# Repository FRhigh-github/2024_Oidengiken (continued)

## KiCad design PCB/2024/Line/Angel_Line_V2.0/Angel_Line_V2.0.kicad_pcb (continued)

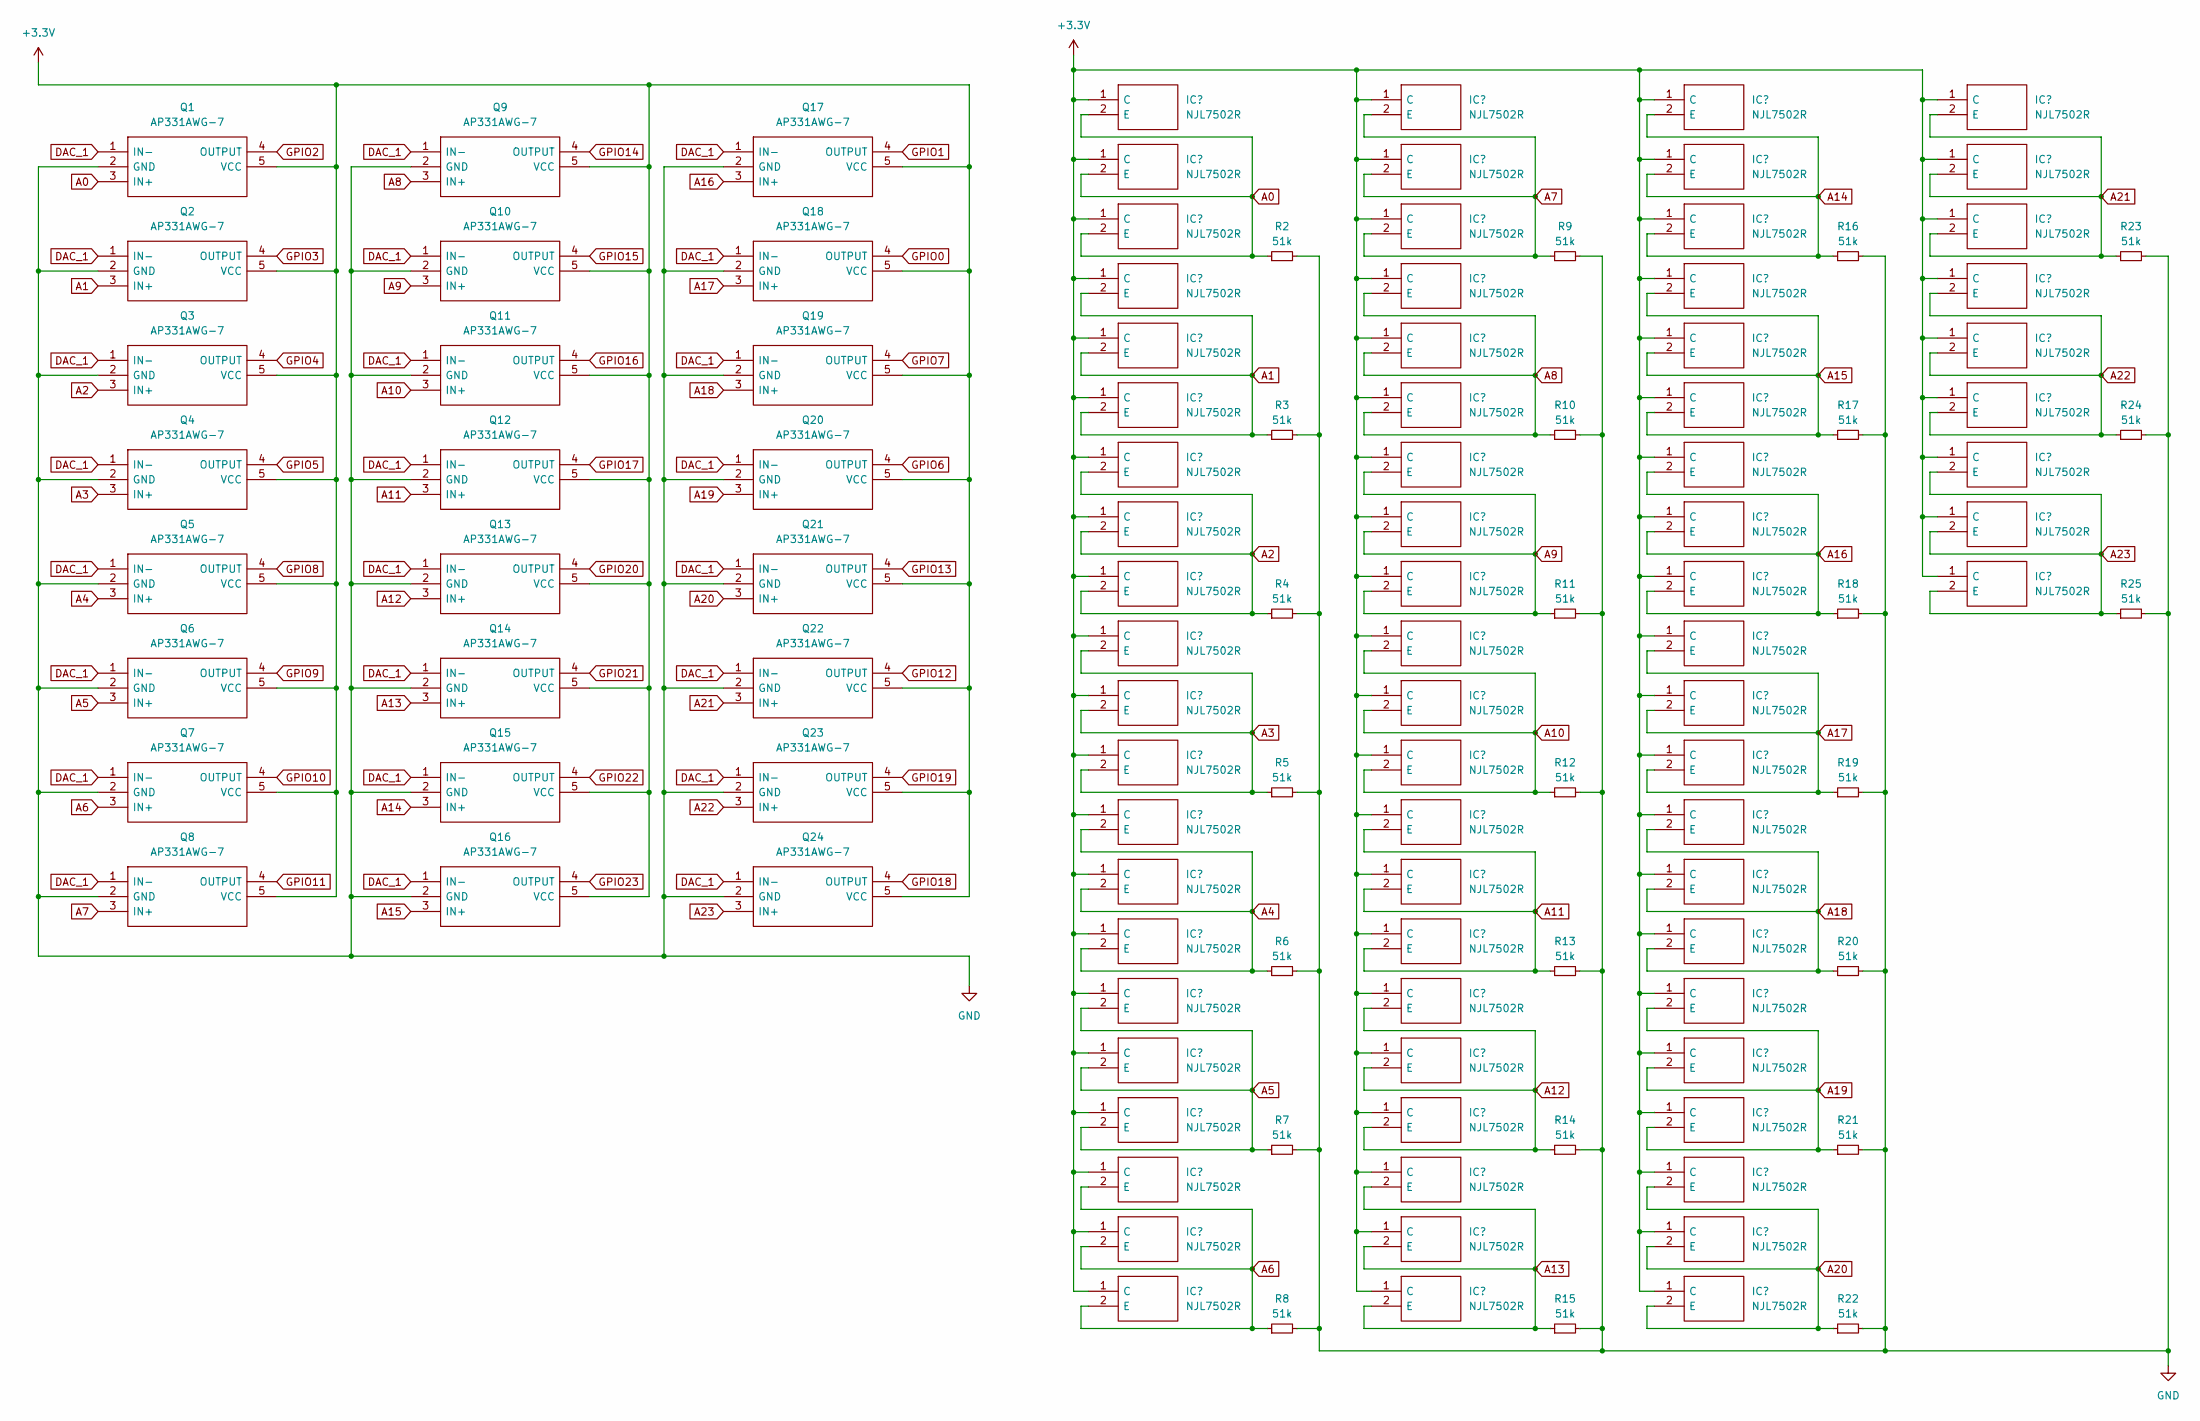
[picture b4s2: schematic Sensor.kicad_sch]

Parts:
IC1, IC2, IC3, IC4, IC5, IC6, IC7, IC8, IC9, IC10, IC11, IC12, IC13, IC14, IC15, IC16, IC17, IC18, IC19, IC20, IC21, IC22, IC23, IC24, IC25, IC26, IC27, IC28, IC29, IC30, IC31, IC32, IC33, IC34, IC35, IC36, IC37, IC38, IC39, IC40, IC41, IC42, IC43, IC44, IC45, IC46, IC47, IC48, IC49, IC50, IC51, IC52, IC53, IC54, IC55, IC56, IC57, IC58, IC59, IC60, IC61, IC62, IC63, IC64, IC65, IC66, IC67, IC68, IC69, IC70, IC71, IC72: NJL7502R; Manufacturer_Part_Number NJL7502R
Q1, Q2, Q3, Q4, Q5, Q6, Q7, Q8, Q9, Q10, Q11, Q12, Q13, Q14, Q15, Q16, Q17, Q18, Q19, Q20, Q21, Q22, Q23, Q24: AP331AWG-7; SOT95P285X130-5N; Mouser Part Number 621-AP331AWG-7
R2, R3, R4, R5, R6, R7, R8, R9, R10, R11, R12, R13, R14, R15, R16, R17, R18, R19, R20, R21, R22, R23, R24, R25: 51k; R_0603_1608Metric

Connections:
+3.3V: IC1.1 (C), IC2.1 (C), IC3.1 (C), IC4.1 (C), IC5.1 (C), IC6.1 (C), IC7.1 (C), IC8.1 (C), IC9.1 (C), IC10.1 (C), IC11.1 (C), IC12.1 (C), IC13.1 (C), IC14.1 (C), IC15.1 (C), IC16.1 (C), IC17.1 (C), IC18.1 (C), IC19.1 (C), IC20.1 (C), IC21.1 (C), IC22.1 (C), IC23.1 (C), IC24.1 (C), IC25.1 (C), IC26.1 (C), IC27.1 (C), IC28.1 (C), IC29.1 (C), IC30.1 (C), IC31.1 (C), IC32.1 (C), IC33.1 (C), IC34.1 (C), IC35.1 (C), IC36.1 (C), IC37.1 (C), IC38.1 (C), IC39.1 (C), IC40.1 (C), IC41.1 (C), IC42.1 (C), IC43.1 (C), IC44.1 (C), IC45.1 (C), IC46.1 (C), IC47.1 (C), IC48.1 (C), IC49.1 (C), IC50.1 (C), IC51.1 (C), IC52.1 (C), IC53.1 (C), IC54.1 (C), IC55.1 (C), IC56.1 (C), IC57.1 (C), IC58.1 (C), IC59.1 (C), IC60.1 (C), IC61.1 (C), IC62.1 (C), IC63.1 (C), IC64.1 (C), IC65.1 (C), IC66.1 (C), IC67.1 (C), IC68.1 (C), IC69.1 (C), IC70.1 (C), IC71.1 (C), IC72.1 (C), Q1.5 (VCC), Q2.5 (VCC), Q3.5 (VCC), Q4.5 (VCC), Q5.5 (VCC), Q6.5 (VCC), Q7.5 (VCC), Q8.5 (VCC), Q9.5 (VCC), Q10.5 (VCC), Q11.5 (VCC), Q12.5 (VCC), Q13.5 (VCC), Q14.5 (VCC), Q15.5 (VCC), Q16.5 (VCC), Q17.5 (VCC), Q18.5 (VCC), Q19.5 (VCC), Q20.5 (VCC), Q21.5 (VCC), Q22.5 (VCC), Q23.5 (VCC), Q24.5 (VCC); also elsewhere on the board
A0: IC1.2 (E), IC2.2 (E), IC3.2 (E), Q1.3 (IN+), R2.1
A1: IC4.2 (E), IC5.2 (E), IC6.2 (E), Q2.3 (IN+), R3.1
A2: IC7.2 (E), IC8.2 (E), IC9.2 (E), Q3.3 (IN+), R4.1
A3: IC10.2 (E), IC11.2 (E), IC12.2 (E), Q4.3 (IN+), R5.1
A4: IC13.2 (E), IC14.2 (E), IC15.2 (E), Q5.3 (IN+), R6.1
A5: IC16.2 (E), IC17.2 (E), IC18.2 (E), Q6.3 (IN+), R7.1
A6: IC19.2 (E), IC20.2 (E), IC21.2 (E), Q7.3 (IN+), R8.1
A7: IC22.2 (E), IC23.2 (E), IC24.2 (E), Q8.3 (IN+), R9.1
A8: IC25.2 (E), IC26.2 (E), IC27.2 (E), Q9.3 (IN+), R10.1
A9: IC28.2 (E), IC29.2 (E), IC30.2 (E), Q10.3 (IN+), R11.1
A10: IC31.2 (E), IC32.2 (E), IC33.2 (E), Q11.3 (IN+), R12.1
A11: IC34.2 (E), IC35.2 (E), IC36.2 (E), Q12.3 (IN+), R13.1
A12: IC37.2 (E), IC38.2 (E), IC39.2 (E), Q13.3 (IN+), R14.1
A13: IC40.2 (E), IC41.2 (E), IC42.2 (E), Q14.3 (IN+), R15.1
A14: IC43.2 (E), IC44.2 (E), IC45.2 (E), Q15.3 (IN+), R16.1
A15: IC46.2 (E), IC47.2 (E), IC48.2 (E), Q16.3 (IN+), R17.1
A16: IC49.2 (E), IC50.2 (E), IC51.2 (E), Q17.3 (IN+), R18.1
A17: IC52.2 (E), IC53.2 (E), IC54.2 (E), Q18.3 (IN+), R19.1
A18: IC55.2 (E), IC56.2 (E), IC57.2 (E), Q19.3 (IN+), R20.1
A19: IC58.2 (E), IC59.2 (E), IC60.2 (E), Q20.3 (IN+), R21.1
A20: IC61.2 (E), IC62.2 (E), IC63.2 (E), Q21.3 (IN+), R22.1
A21: IC64.2 (E), IC65.2 (E), IC66.2 (E), Q22.3 (IN+), R23.1
A22: IC67.2 (E), IC68.2 (E), IC69.2 (E), Q23.3 (IN+), R24.1
A23: IC70.2 (E), IC71.2 (E), IC72.2 (E), Q24.3 (IN+), R25.1
DAC_1: Q1.1 (IN-), Q2.1 (IN-), Q3.1 (IN-), Q4.1 (IN-), Q5.1 (IN-), Q6.1 (IN-), Q7.1 (IN-), Q8.1 (IN-), Q9.1 (IN-), Q10.1 (IN-), Q11.1 (IN-), Q12.1 (IN-), Q13.1 (IN-), Q14.1 (IN-), Q15.1 (IN-), Q16.1 (IN-), Q17.1 (IN-), Q18.1 (IN-), Q19.1 (IN-), Q20.1 (IN-), Q21.1 (IN-), Q22.1 (IN-), Q23.1 (IN-), Q24.1 (IN-); also elsewhere on the board
GND: Q1.2 (GND), Q2.2 (GND), Q3.2 (GND), Q4.2 (GND), Q5.2 (GND), Q6.2 (GND), Q7.2 (GND), Q8.2 (GND), Q9.2 (GND), Q10.2 (GND), Q11.2 (GND), Q12.2 (GND), Q13.2 (GND), Q14.2 (GND), Q15.2 (GND), Q16.2 (GND), Q17.2 (GND), Q18.2 (GND), Q19.2 (GND), Q20.2 (GND), Q21.2 (GND), Q22.2 (GND), Q23.2 (GND), Q24.2 (GND), R2.2, R3.2, R4.2, R5.2, R6.2, R7.2, R8.2, R9.2, R10.2, R11.2, R12.2, R13.2, R14.2, R15.2, R16.2, R17.2, R18.2, R19.2, R20.2, R21.2, R22.2, R23.2, R24.2, R25.2; also elsewhere on the board
GPIO0: Q18.4 (OUTPUT); also elsewhere on the board
GPIO1: Q17.4 (OUTPUT); also elsewhere on the board
GPIO2: Q1.4 (OUTPUT); also elsewhere on the board
GPIO3: Q2.4 (OUTPUT); also elsewhere on the board
GPIO4: Q3.4 (OUTPUT); also elsewhere on the board
GPIO5: Q4.4 (OUTPUT); also elsewhere on the board
GPIO6: Q20.4 (OUTPUT); also elsewhere on the board
GPIO7: Q19.4 (OUTPUT); also elsewhere on the board
GPIO8: Q5.4 (OUTPUT); also elsewhere on the board
GPIO9: Q6.4 (OUTPUT); also elsewhere on the board
GPIO10: Q7.4 (OUTPUT); also elsewhere on the board
GPIO11: Q8.4 (OUTPUT); also elsewhere on the board
GPIO12: Q22.4 (OUTPUT); also elsewhere on the board
GPIO13: Q21.4 (OUTPUT); also elsewhere on the board
GPIO14: Q9.4 (OUTPUT); also elsewhere on the board
GPIO15: Q10.4 (OUTPUT); also elsewhere on the board
GPIO16: Q11.4 (OUTPUT); also elsewhere on the board
GPIO17: Q12.4 (OUTPUT); also elsewhere on the board
GPIO18: Q24.4 (OUTPUT); also elsewhere on the board
GPIO19: Q23.4 (OUTPUT); also elsewhere on the board
GPIO20: Q13.4 (OUTPUT); also elsewhere on the board
GPIO21: Q14.4 (OUTPUT); also elsewhere on the board
GPIO22: Q15.4 (OUTPUT); also elsewhere on the board
GPIO23: Q16.4 (OUTPUT); also elsewhere on the board

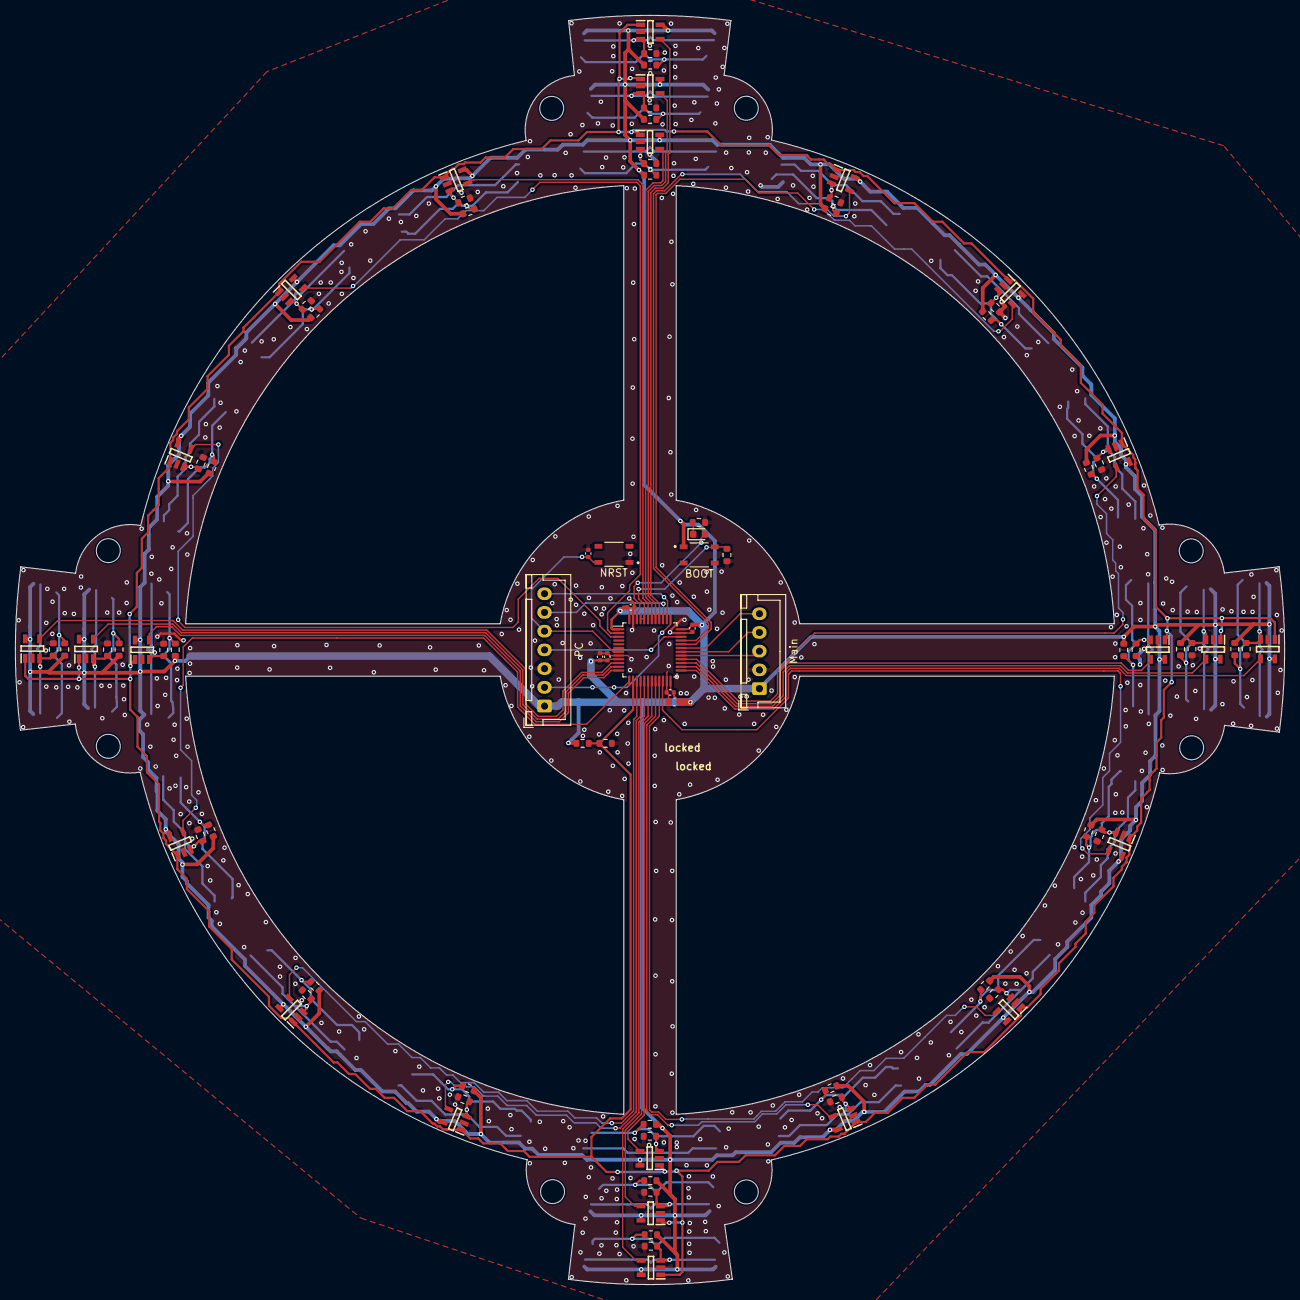
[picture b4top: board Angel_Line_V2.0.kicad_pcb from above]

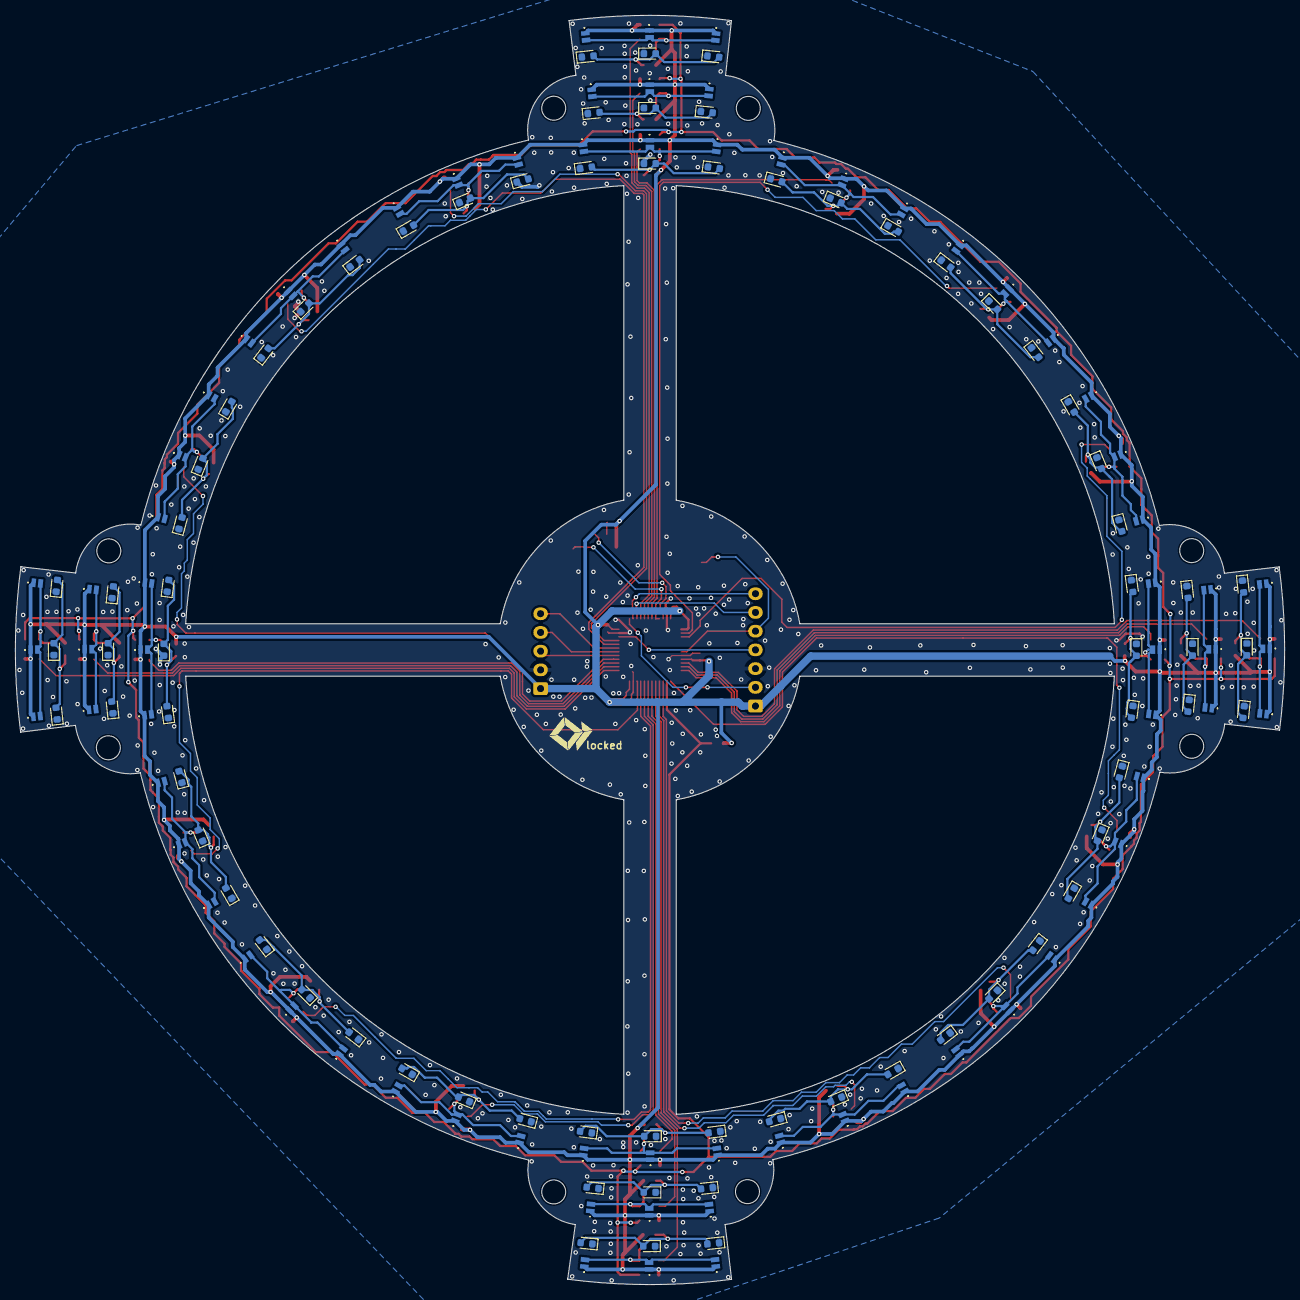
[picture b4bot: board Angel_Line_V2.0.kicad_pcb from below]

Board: 2 copper layers, 169.5 x 169.5 mm, 233 parts (144 on the bottom side), 86 nets.

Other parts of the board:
BOOT: BOOT; SW_SKRPABE010
Main: Main; JST_XH_B5B-XH-A_1x05_P2.50mm_Vertical
NRST: NRST; SW_SKRPABE010
PC: PC; JST_XH_B7B-XH-A_1x07_P2.50mm_Vertical

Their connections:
+3.3V: BOOT.1, Main.1, PC.1; also elsewhere on the board
BOOT: BOOT.2; also elsewhere on the board
GND: Main.2, NRST.1, PC.3; also elsewhere on the board
NRST: NRST.2, PC.5; also elsewhere on the board
SWCLK: PC.2; also elsewhere on the board
SWDIO: PC.4; also elsewhere on the board
USART1_CK: Main.3; also elsewhere on the board
USART1_RX: Main.5; also elsewhere on the board
USART1_TX: Main.4; also elsewhere on the board
USART2_RX: PC.7; also elsewhere on the board
USART2_TX: PC.6; also elsewhere on the board

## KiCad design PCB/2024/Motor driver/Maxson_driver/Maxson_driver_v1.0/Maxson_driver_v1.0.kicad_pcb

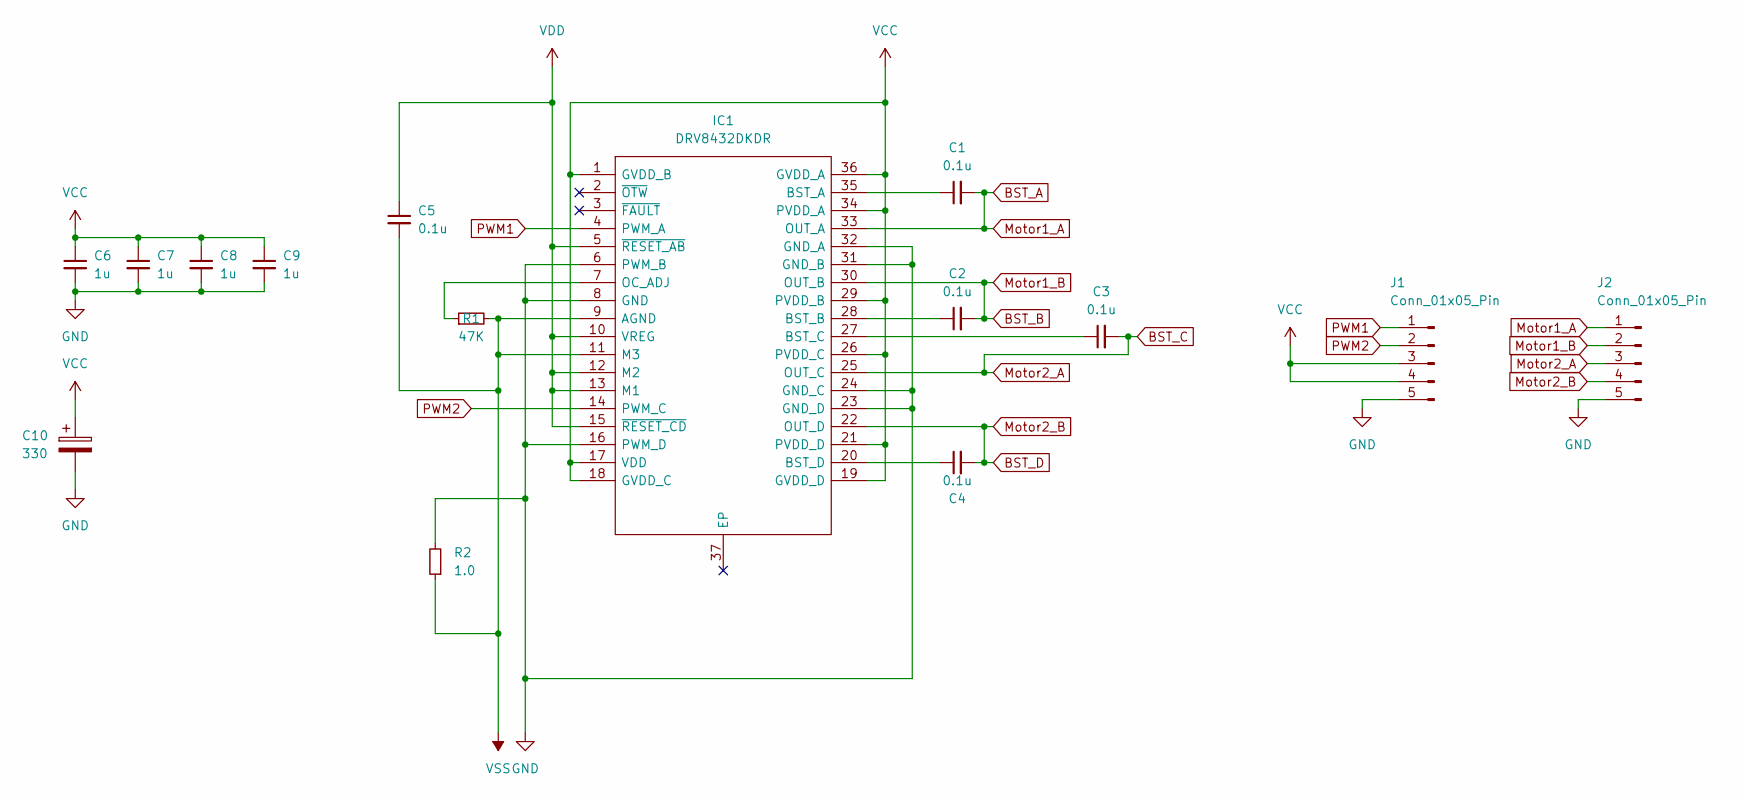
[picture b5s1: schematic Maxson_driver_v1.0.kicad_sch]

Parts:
C1, C2, C3, C4, C5: 0.1u; C_0402_1005Metric
C6, C7, C8, C9: 1u; C_0402_1005Metric
C10: 330; CP_Radial_D8.0mm_P5.00mm
IC1: DRV8432DKDR; SOP65P1420X360-37N; Manufacturer_Part_Number DRV8432DKDR
J1, J2: Conn_01x05_Pin; PinHeader_1x05_P2.54mm_Vertical
R1: 47K; R_0402_1005Metric
R2: 1.0; R_0805_2012Metric

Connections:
BST_A: C1.2, IC1.33 (OUT_A), J2.1
BST_B: C2.2, IC1.30 (OUT_B), J2.2
BST_C: C3.2, IC1.25 (OUT_C), J2.3
BST_D: C4.2, IC1.22 (OUT_D), J2.4
GND: C6.2, C7.2, C8.2, C9.2, C10.2, IC1.6 (PWM_B), IC1.8 (GND), IC1.16 (PWM_D), IC1.23 (GND_D), IC1.24 (GND_C), IC1.31 (GND_B), IC1.32 (GND_A), J1.5, J2.5, R2.2
unnamed: C1.1, IC1.35 (BST_A)
unnamed: C2.1, IC1.28 (BST_B)
unnamed: C3.1, IC1.27 (BST_C)
unnamed: C4.1, IC1.20 (BST_D)
unnamed: IC1.7 (OC_ADJ), R1.1
PWM1: IC1.4 (PWM_A), J1.1
PWM2: IC1.14 (PWM_C), J1.2
VCC: C6.1, C7.1, C8.1, C9.1, C10.1, IC1.1 (GVDD_B), IC1.17 (VDD), IC1.18 (GVDD_C), IC1.19 (GVDD_D), IC1.21 (PVDD_D), IC1.26 (PVDD_C), IC1.29 (PVDD_B), IC1.34 (PVDD_A), IC1.36 (GVDD_A), J1.3, J1.4
VDD: C5.1, IC1.5 (~RESET_AB), IC1.10 (VREG), IC1.12 (M2), IC1.13 (M1), IC1.15 (~RESET_CD)
VSS: C5.2, IC1.9 (AGND), IC1.11 (M3), R1.2, R2.1

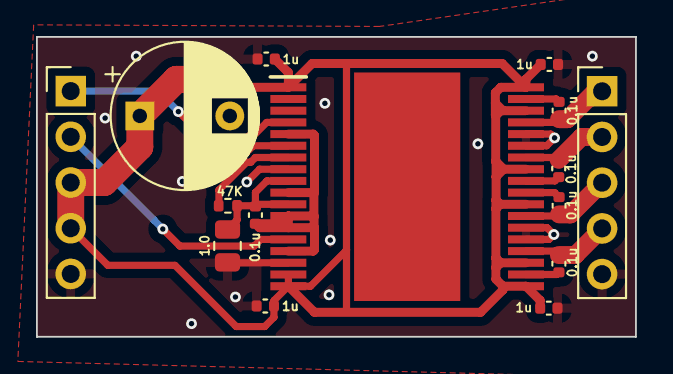
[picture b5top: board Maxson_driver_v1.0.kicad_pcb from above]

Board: 2 copper layers, 33.3 x 16.7 mm, 15 parts (0 on the bottom side), 15 nets.

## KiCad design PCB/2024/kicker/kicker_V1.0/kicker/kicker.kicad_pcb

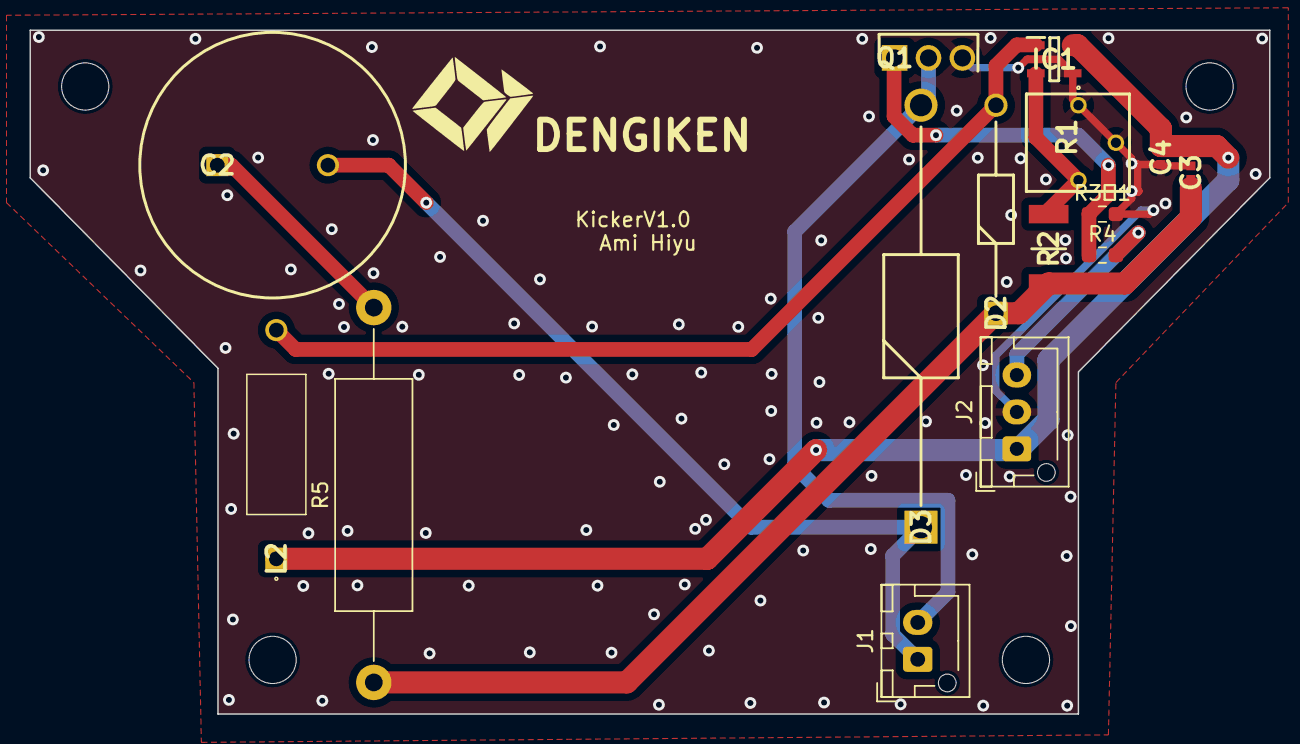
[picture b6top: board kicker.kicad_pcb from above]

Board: 2 copper layers, 84.0 x 46.3 mm, 15 parts (0 on the bottom side), 10 nets.

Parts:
C2: 860010681031; CAPPRD750W82D1800H4300
C3, C4: GRM155R6YA105KE11D; CAPC1005X55N
D2: 1N5819RL; DIOAD1414W86L464D238
D3: SBM1045VSS; DIOAD2855W130L835D505
IC1: AP3012KTR-G1; SOT95P280X145-5N
J1: Conn_01x02_Pin; JST_XH_B2B-XH-AM_1x02_P2.50mm_Vertical
J2: Conn_01x03_Pin; JST_XH_B3B-XH-AM_1x03_P2.50mm_Vertical
L2: B78108E1103K009; B78108E
Q1: 2SK4017_Q_; TO230P250X650X900-3P
R1: 3362P-1-503LF; 3362P_1
R2: CMP2010-FX-1003ELF 100k; RESC5025X70N
R3　1, R4: R; R_0603_1608Metric_Pad0.98x0.95mm_HandSolder
R5: 220Ω; R_Axial_DIN0516_L15.5mm_D5.0mm_P25.40mm_Horizontal

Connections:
+12V: C4.1, IC1.5 (VIN), J2.1, L2.1
+24V: C3.1, D2.1, R2.1, R5.1
GND: C3.2, C4.2, IC1.2 (GND), IC1.4 (~SHDN), J2.2, Q1.3 (SOURCE), R1.1 (CCW), R1.2 (WIPER), R3 1.2
GPIO: J2.3, R4.2
unnamed: C2.1, R5.2
unnamed: IC1.3 (FB), R1.3 (CW), R2.2
unnamed: D2.2, IC1.1 (SW), L2.2
unnamed: C2.2, D3.1, J1.1
unnamed: D3.2, J1.2, Q1.2 (DRAIN)
unnamed: Q1.1 (GATE), R3 1.1, R4.1

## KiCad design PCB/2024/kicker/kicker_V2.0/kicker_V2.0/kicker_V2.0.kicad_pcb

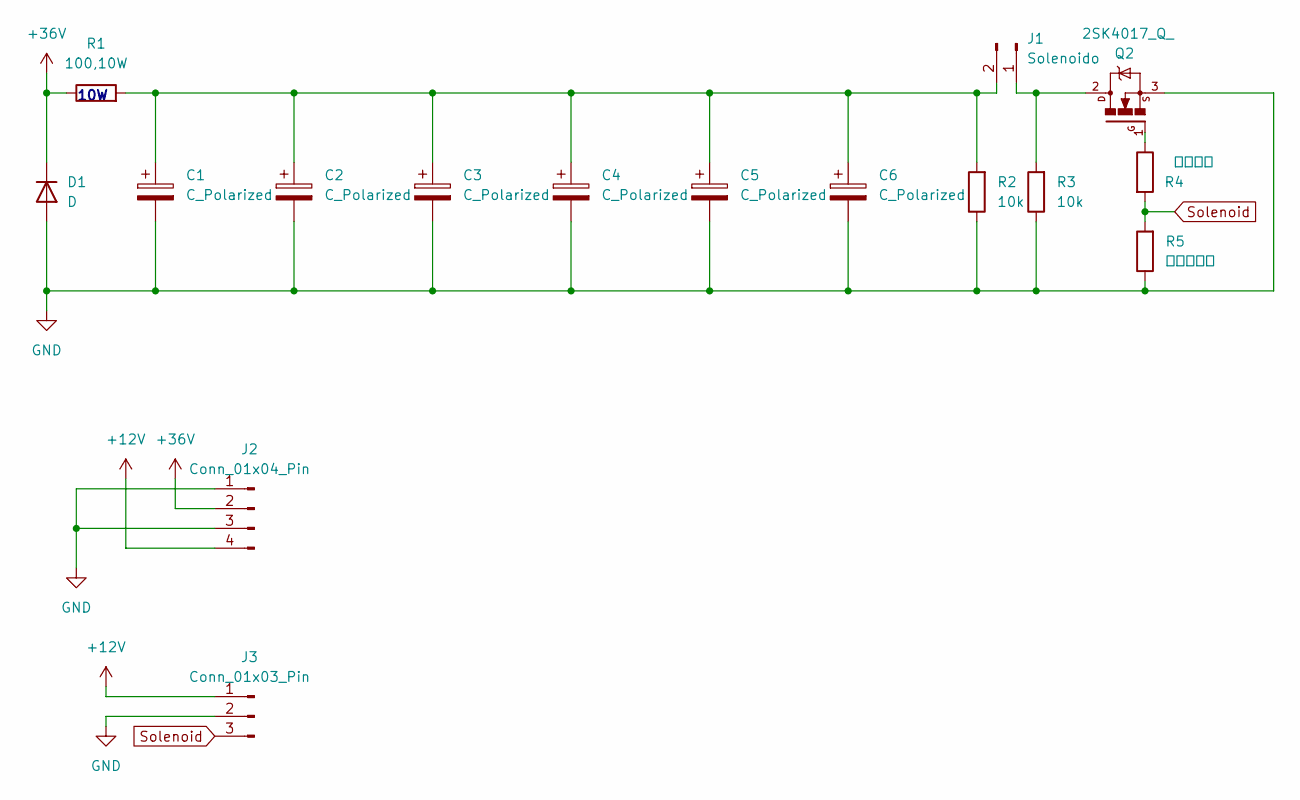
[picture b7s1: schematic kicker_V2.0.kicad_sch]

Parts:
C1, C2, C3, C4, C5, C6: C_Polarized; C_Radial_D12.5mm_H20.0mm_P5.00mm
D1: D; D_SMB_Handsoldering
J1: Solenoido; JST_XH_B2B-XH-AM_1x02_P2.50mm_Vertical
J2: Conn_01x04_Pin; Kicker
J3: Conn_01x03_Pin; JST_XH_B3B-XH-AM_1x03_P2.50mm_Vertical
Q2: 2SK4017_Q_; TO230P250X650X900-3P
R1: 100,10W; R_Axial_Power_L48.0mm_W12.5mm_P55.88mm
R2, R3: 10k; R_Axial_DIN0207_L6.3mm_D2.5mm_P10.16mm_Horizontal
R4: 電流制限; R_0603_1608Metric
R5: プルダウン; R_0603_1608Metric

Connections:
+12V: J2.4, J3.1
+36V: D1.1 (K), J2.2, R1.1
GND: C1.2, C2.2, C3.2, C4.2, C5.2, C6.2, D1.2 (A), J2.1, J2.3, J3.2, Q2.3, R2.1, R3.1, R5.1
unnamed: J1.1, Q2.2, R3.2
unnamed: C1.1, C2.1, C3.1, C4.1, C5.1, C6.1, J1.2, R1.2, R2.2
unnamed: Q2.1, R4.1
Solenoid: J3.3, R4.2, R5.2

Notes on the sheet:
10W

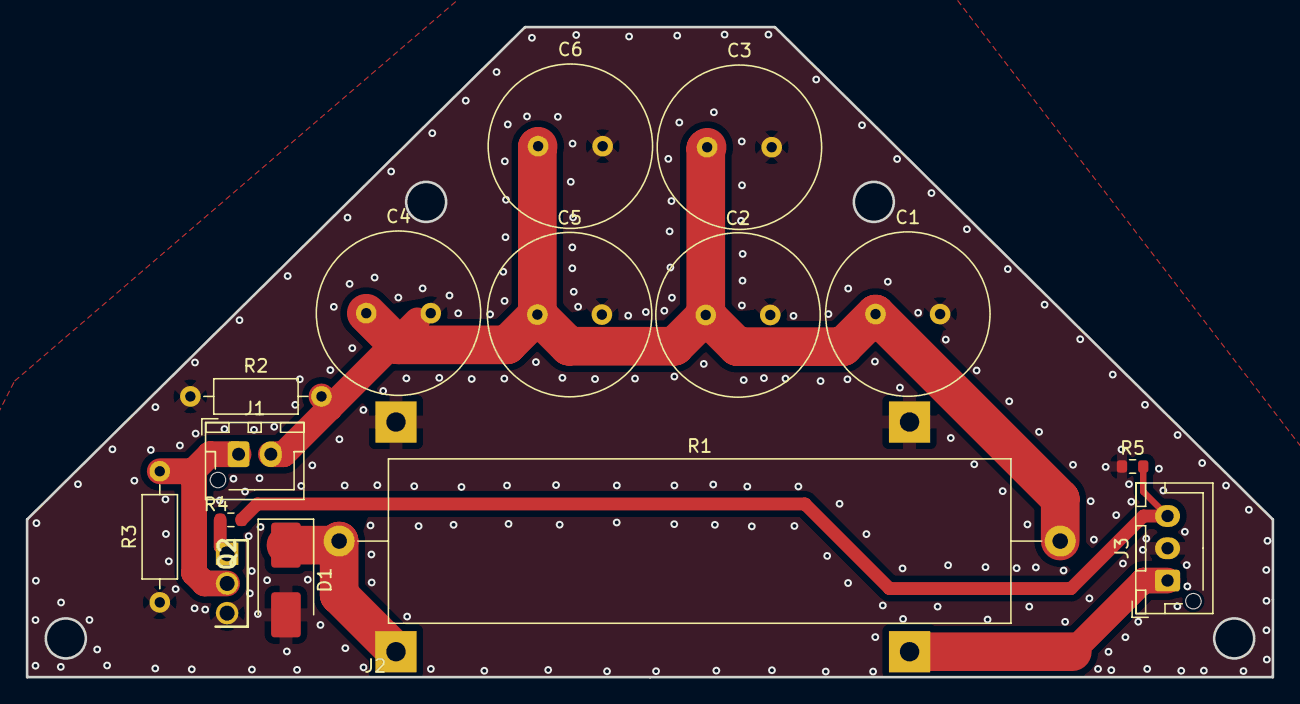
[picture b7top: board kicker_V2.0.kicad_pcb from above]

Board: 2 copper layers, 96.5 x 50.4 mm, 16 parts (0 on the bottom side), 7 nets.
